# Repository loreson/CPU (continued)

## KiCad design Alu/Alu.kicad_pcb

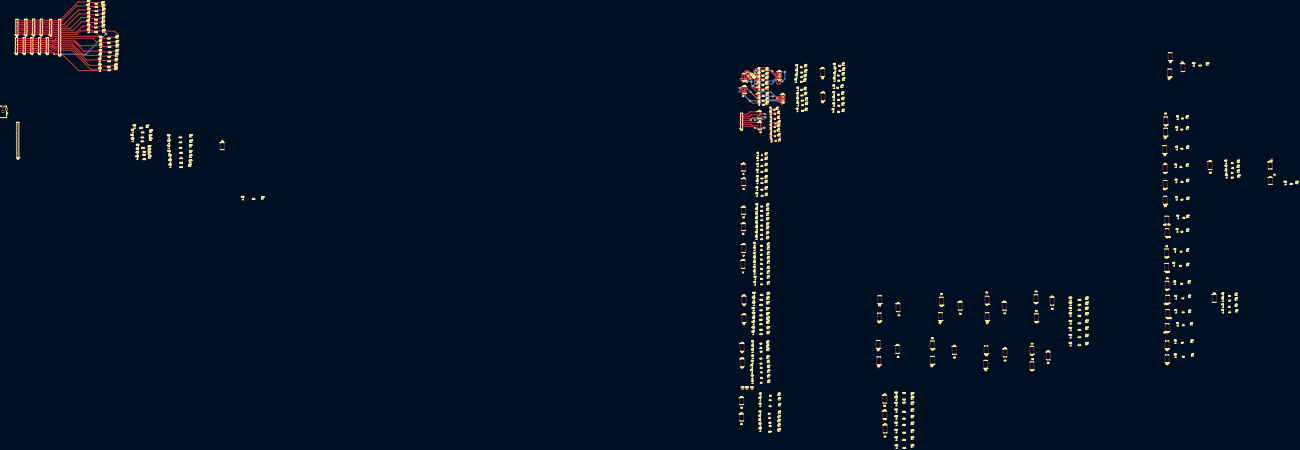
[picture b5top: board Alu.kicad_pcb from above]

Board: 4 copper layers, 642 parts (0 on the bottom side), 508 nets.

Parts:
C1, C2, C3, C4, C5, C8, C9, C10, C11, C12, C13, C14, C15, C16, C17, C18, C19, C20, C21, C22, C23, C24, C25, C26, C27, C28, C29, C30, C31, C32, C33, C34, C35, C36, C37, C38, C39, C40, C41, C42, C43, C44, C45, C46, C47, C48, C49, C50, C51, C52, C53, C54, C55, C56, C57, C58, C59, C60, C61, C62, C63, C64, C65, C66, C67, C68, C69, C70, C71: 100nF; C_0805_2012Metric
C6, C7: 100nF; C_0805_2012Metric_Pad1.29x1.40mm_HandSolder
D1, D2, D3, D4, D5, D6, D7, D8, D9, D10, D11, D12, D13, D14, D15, D16, D17, D18, D19, D20, D21, D22, D23, D24, D25, D26, D27, D28, D29, D30, D31, D32, D33, D34, D35, D36, D37, D38, D39, D40, D41, D42, D43, D44, D45, D46, D47, D48, D50, D51, D52, D53, D54, D55, D56, D58, D59, D60, D61, D62, D63, D64, D65, D66, D68, D69, D70, D71, D72, D73, D74, D75, D77, D78, D79, D80, D81, D82, D83, D84, D85, D86, D87, D88, D89, D90, D91, D92, D93, D94, D95, D96, D97, D98, D99, D100, D101, D102, D103, D104, D105, D106, D107, D108, D109, D110, D111, D112, D113, D114, D115, D116, D118, D119, D120, D121, D122, D123, D124, D125, D126, D127, D128, D129, D130, D131, D132, D133, D139, D140, D141, D142, D143, D144, D145, D146, D147, D148, D149, D150, D151, D152, D153, D154: RED; LED_0805_2012Metric_Pad1.12x1.40mm_HandSolder
D49, D57, D67, D76, D117, D134, D163, D164, D165, D167, D168: BLUE; LED_0805_2012Metric_Pad1.12x1.40mm_HandSolder
D135, D136, D137, D138, D166: GREEN; LED_0805_2012Metric_Pad1.12x1.40mm_HandSolder
J1, J3, J5, J6, J7, J9, J10, J11, J12, J13, J14: Conn_01x08; PinHeader_1x08_P2.54mm_Vertical_SMD_Pin1Right
J2: Barrel_Jack; BarrelJack_Horizontal
J4, J8: Conn_01x18; PinHeader_1x18_P2.54mm_Vertical_SMD_Pin1Left
Q1, Q2, Q3, Q4, Q5, Q6, Q7, Q8, Q9, Q10, Q11, Q12, Q13, Q14, Q15, Q16, Q17, Q18, Q19, Q20, Q21, Q22, Q23, Q24, Q25, Q26, Q27, Q28, Q29, Q30, Q31, Q32, Q33, Q34, Q35, Q36, Q37, Q38, Q39, Q40, Q41, Q42, Q43, Q44, Q45, Q46, Q47, Q48, Q49, Q50, Q51, Q52, Q53, Q54, Q55, Q56, Q57, Q58, Q59, Q60, Q61, Q62, Q63, Q64, Q65, Q66, Q67, Q68, Q69, Q70, Q71, Q72, Q73, Q74, Q75, Q76, Q77, Q78, Q79, Q80, Q81, Q82, Q83, Q84, Q85, Q86, Q87, Q88, Q89, Q90, Q91, Q92, Q93, Q94, Q95, Q96, Q97, Q98, Q99, Q100, Q101, Q102, Q103, Q104, Q105, Q106, Q107, Q108, Q109, Q110, Q111, Q112, Q113, Q114, Q115, Q116, Q117, Q118, Q119, Q120, Q121, Q122, Q123, Q124, Q125, Q126, Q127, Q128, Q129, Q130, Q131, Q132, Q133, Q134, Q135, Q136, Q137, Q138, Q139, Q140, Q141, Q142, Q143, Q144, Q145, Q146, Q147, Q148, Q149, Q150, Q151, Q152, Q153, Q154, Q163, Q164, Q165, Q166, Q167, Q168: 2N7002; SOT-23
R1, R2, R3, R4, R5, R6, R7, R8, R9, R10, R11, R12, R13, R14, R15, R16, R17, R18, R19, R20, R21, R22, R23, R24, R25, R26, R27, R28, R29, R30, R31, R32, R33, R34, R35, R36, R37, R38, R39, R40, R41, R42, R43, R44, R45, R46, R47, R48, R50, R51, R52, R53, R54, R55, R56, R58, R59, R60, R61, R62, R63, R64, R65, R66, R68, R69, R70, R71, R72, R73, R74, R75, R77, R78, R79, R80, R81, R82, R83, R84, R85, R86, R87, R88, R89, R90, R91, R92, R93, R94, R95, R96, R97, R98, R99, R100, R101, R102, R103, R104, R105, R106, R107, R108, R109, R110, R111, R112, R113, R114, R115, R116, R118, R119, R120, R121, R122, R123, R124, R125, R126, R127, R128, R129, R130, R131, R132, R133, R139, R140, R141, R142, R143, R144, R145, R146, R147, R148, R149, R150, R151, R152, R153, R154: 1k; R_0805_2012Metric
R49, R57, R67, R76, R117, R134, R163, R164, R165, R167, R168: 820R; R_0805_2012Metric_Pad1.29x1.40mm_HandSolder
R135, R136, R137, R138, R166: 1k; R_0805_2012Metric_Pad1.29x1.40mm_HandSolder
R155, R156: 0; R_1206_3216Metric_Pad1.39x1.80mm_HandSolder
R157, R158, R159, R160: 0; R_1806_4516Metric
U1, U5, U6: 74LS08; SOIC-14_3.9x8.7mm_P1.27mm
U2, U3: 74HC02; SOIC-14_3.9x8.7mm_P1.27mm
U4, U7: 74LS32; SOIC-14_3.9x8.7mm_P1.27mm
U8, U10, U11, U13, U14, U16, U17, U19, U20, U22, U23, U25, U26, U28, U29, U31, U32, U34: 74LS151; SOIC-16_3.9x9.9mm_P1.27mm
U9, U12, U15, U18, U21, U24, U27, U30, U33, U35, U36, U37, U53, U54: 74LS157; SOIC-16_3.9x9.9mm_P1.27mm
U41, U42, U71, U72: 74HC04; SOIC-14_3.9x8.7mm_P1.27mm
U43, U44: 74HC86; SOIC-14_3.9x8.7mm_P1.27mm
U45, U46, U47, U48, U49, U50, U51, U52, U73, U74: 74LS283; SOIC-16_3.9x9.9mm_P1.27mm
U55, U56, U57, U58, U59, U60, U61, U62, U63, U64, U65, U66, U67, U68, U69, U70: 74LS251; SOIC-16_3.9x9.9mm_P1.27mm

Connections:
/8-BIT_16-1MUX/16-2MUX0/Z0: Q68.1, U53.2, U55.5
/8-BIT_16-1MUX/16-2MUX0/Z1: Q69.1, U53.3, U56.5
/8-BIT_16-1MUX/16-2MUX1/Z0: Q70.1, U53.5, U57.5
/8-BIT_16-1MUX/16-2MUX1/Z1: Q71.1, U53.6, U58.5
/8-BIT_16-1MUX/16-2MUX2/Z0: Q72.1, U53.14, U59.5
/8-BIT_16-1MUX/16-2MUX2/Z1: Q73.1, U53.13, U60.5
/8-BIT_16-1MUX/16-2MUX3/Z0: Q74.1, U53.11, U61.5
/8-BIT_16-1MUX/16-2MUX3/Z1: Q75.1, U53.10, U62.5
/8-BIT_16-1MUX/16-2MUX4/Z0: Q77.1, U54.2, U63.5
/8-BIT_16-1MUX/16-2MUX4/Z1: Q78.1, U54.3, U64.5
/8-BIT_16-1MUX/16-2MUX5/Z0: Q79.1, U54.5, U65.5
/8-BIT_16-1MUX/16-2MUX5/Z1: Q80.1, U54.6, U66.5
/8-BIT_16-1MUX/16-2MUX6/Z0: Q81.1, U54.14, U67.5
/8-BIT_16-1MUX/16-2MUX6/Z1: Q82.1, U54.13, U68.5
/8-BIT_16-1MUX/16-2MUX7/Z0: Q83.1, U54.11, U69.5
/8-BIT_16-1MUX/16-2MUX7/Z1: Q84.1, U54.10, U70.5
/Bit0_X0: Q59.1, U51.4, U55.4
/Bit0_X1: Q8.1, U5.3, U55.3
/Bit0_X2: Q9.1, U4.3, U55.2
/Bit0_X3: Q25.1, U43.3, U55.1
/Bit0_X4: Q41.1, U47.4, U55.15
/Bit0_X5: Q101.1, U55.14, U73.4
/Bit0_X6: Q50.1, U49.4, U55.13
/Bit0_X7: Q93.1, R159.1, U55.12
/Bit0_X8: Q109.1, U12.4, U56.3, U56.4
/Bit0_X10: J1.8, J3.8, J5.8, J6.8, J7.8, J8.18, J14.8, Q147.1, U4.1, U5.1, U11.4, U13.4, U16.3, U19.2, U22.1, U25.15, U28.14, U31.13, U34.12, U35.2, U36.6, U43.1, U47.5, U49.5, U51.5, U56.2, U71.1, U73.5
/Bit0_X11: Q118.1, U36.4, U56.1, U56.15
/Bit1_X0: Q60.1, U51.1, U57.4
/Bit1_X1: Q1.1, U5.6, U57.3
/Bit1_X2: Q10.1, U4.6, U57.2
/Bit1_X3: Q26.1, U43.6, U57.1
/Bit1_X4: Q42.1, U47.1, U57.15
/Bit1_X5: Q102.1, U57.14, U73.1
/Bit1_X6: Q51.1, U49.1, U57.13
/Bit1_X7: Q94.1, R160.1, U57.12
/Bit1_X8: Q110.1, U15.4, U58.3, U58.4
/Bit1_X10: J1.7, J3.7, J5.7, J6.7, J7.7, J8.17, J14.7, Q148.1, U4.4, U5.4, U11.3, U14.4, U16.4, U19.3, U22.2, U25.1, U28.15, U31.14, U34.13, U36.2, U36.13, U43.4, U47.3, U49.3, U51.3, U58.2, U71.3, U73.3
/Bit1_X11: Q119.1, U36.7, U58.1, U58.15
/Bit2_X0: Q61.1, U51.13, U59.4
/Bit2_X1: Q2.1, U5.8, U59.3
/Bit2_X2: Q11.1, U4.8, U59.2
/Bit2_X3: Q27.1, U43.8, U59.1
/Bit2_X4: Q43.1, U47.13, U59.15
/Bit2_X5: Q103.1, U59.14, U73.13
/Bit2_X6: Q52.1, U49.13, U59.13
/Bit2_X7: Q95.1, R156.1, U59.12
/Bit2_X8: Q111.1, U18.4, U60.3, U60.4
/Bit2_X10: J1.6, J3.6, J5.6, J6.6, J7.6, J8.16, J14.6, Q149.1, U4.9, U5.9, U11.2, U14.3, U17.4, U19.4, U22.3, U25.2, U28.1, U31.15, U34.14, U36.5, U36.10, U43.9, U47.14, U49.14, U51.14, U60.2, U71.5, U73.14
/Bit2_X11: Q120.1, U36.12, U60.1, U60.15
/Bit3_X0: Q62.1, U51.10, U61.4
/Bit3_X1: Q3.1, U5.11, U61.3
/Bit3_X2: Q12.1, U4.11, U61.2
/Bit3_X3: Q28.1, U43.11, U61.1
/Bit3_X4: Q44.1, U47.10, U61.15
/Bit3_X5: Q104.1, U61.14, U73.10
/Bit3_X6: Q53.1, U49.10, U61.13
/Bit3_X7: Q96.1, U61.12, U71.8
/Bit3_X8: Q112.1, U21.4, U62.3, U62.4
/Bit3_X10: J1.5, J3.5, J5.5, J6.5, J7.5, J8.15, J14.5, Q150.1, U4.12, U5.12, U11.1, U14.2, U17.3, U20.4, U22.4, U25.3, U28.2, U31.1, U34.15, U36.14, U37.3, U43.12, U47.12, U49.12, U51.12, U62.2, U71.9, U73.12
/Bit3_X11: Q121.1, U36.9, U62.1, U62.15
/Bit4_X0: Q63.1, U52.4, U63.4
/Bit4_X1: Q4.1, U6.3, U63.3
/Bit4_X2: Q13.1, U7.3, U63.2
/Bit4_X3: Q29.1, U44.3, U63.1
/Bit4_X4: Q45.1, U48.4, U63.15
/Bit4_X5: Q105.1, U63.14, U74.4
/Bit4_X6: Q54.1, U50.4, U63.13
/Bit4_X7: Q97.1, U63.12, U71.10
/Bit4_X8: Q113.1, U24.4, U64.3, U64.4
/Bit4_X10: J1.4, J3.4, J5.4, J6.4, J7.4, J8.14, J14.4, Q151.1, U6.1, U7.1, U11.15, U14.1, U17.2, U20.3, U23.4, U25.4, U28.3, U31.2, U34.1, U36.11, U37.6, U44.1, U48.5, U50.5, U52.5, U64.2, U71.11, U74.5
/Bit4_X11: Q122.1, U37.4, U64.1, U64.15
/Bit5_X0: Q64.1, U52.1, U65.4
/Bit5_X1: Q5.1, U6.6, U65.3
/Bit5_X2: Q14.1, U7.6, U65.2
/Bit5_X3: Q30.1, U44.6, U65.1
/Bit5_X4: Q46.1, U48.1, U65.15
/Bit5_X5: Q106.1, U65.14, U74.1
/Bit5_X6: Q55.1, U50.1, U65.13
/Bit5_X7: Q98.1, U65.12, U71.12
/Bit5_X8: Q114.1, U27.4, U66.3, U66.4
/Bit5_X10: J1.3, J3.3, J5.3, J6.3, J7.3, J8.13, J14.3, Q152.1, U6.4, U7.4, U11.14, U14.15, U17.1, U20.2, U23.3, U26.4, U28.4, U31.3, U34.2, U37.2, U37.13, U44.4, U48.3, U50.3, U52.3, U66.2, U71.13, U74.3
/Bit5_X11: Q123.1, U37.7, U66.1, U66.15
/Bit6_X0: Q65.1, U52.13, U67.4
/Bit6_X1: Q6.1, U6.8, U67.3
/Bit6_X2: Q15.1, U7.8, U67.2
/Bit6_X3: Q31.1, U44.8, U67.1
/Bit6_X4: Q47.1, U48.13, U67.15
/Bit6_X5: Q107.1, U67.14, U74.13
/Bit6_X6: Q56.1, U50.13, U67.13
/Bit6_X7: Q99.1, U67.12, U72.2
/Bit6_X8: Q115.1, U30.4, U68.3, U68.4
/Bit6_X10: J1.2, J3.2, J5.2, J6.2, J7.2, J8.12, J14.2, Q153.1, U6.9, U7.9, U11.13, U14.14, U17.15, U20.1, U23.2, U26.3, U29.4, U31.4, U34.3, U37.5, U37.10, U44.9, U48.14, U50.14, U52.14, U68.2, U72.1, U74.14
/Bit6_X11: Q124.1, U37.12, U68.1, U68.15
/Bit7_X0: Q66.1, U52.10, U69.4
/Bit7_X1: Q7.1, U6.11, U69.3
/Bit7_X2: Q16.1, U7.11, U69.2
/Bit7_X3: Q32.1, U44.11, U69.1
/Bit7_X4: Q48.1, U48.10, U69.15
/Bit7_X5: Q108.1, U69.14, U74.10
/Bit7_X6: Q58.1, U50.10, U69.13
/Bit7_X7: Q100.1, U69.12, U72.4
/Bit7_X8: Q116.1, U33.4, U70.3, U70.4
/Bit7_X10: J1.1, J3.1, J5.1, J6.1, J7.1, J8.11, J14.1, Q154.1, U6.12, U7.12, U11.12, U14.13, U17.14, U20.15, U23.1, U26.2, U29.3, U32.4, U34.4, U35.3, U37.14, U44.12, U48.12, U50.12, U52.12, U70.2, U72.3, U74.12
/Bit7_X11: Q125.1, U37.9, U70.1, U70.15
/Cin: J4.18, Q165.1, U1.1
/CinE: J4.17, Q166.1, U1.2
/CinL: U1.3, U36.3, U37.11, U49.7, U51.7
/Cout: J4.16, Q163.1, Q168.1, U9.4
/Cout12-13: Q134.1, U10.14, U10.15, U35.4
/Cout_0: Q76.1, U8.4, U52.9
/Cout_4: Q57.1, U8.15, U48.9
/Cout_5: Q117.1, U8.14, U74.9
/Cout_6: Q67.1, U8.13, U50.9
/S0: J4.14, Q138.1, U9.1, U12.1, U15.1, U18.1, U21.1, U24.1, U27.1, U30.1, U33.1, U35.1, U36.1, U37.1, U53.1, U54.1
/S1: J4.13, Q137.1, U8.11, U10.11, U55.11, U56.11, U57.11, U58.11, U59.11, U60.11, U61.11, U62.11, U63.11, U64.11, U65.11, U66.11, U67.11, U68.11, U69.11, U70.11
/S2: J4.12, Q136.1, U8.10, U10.10, U55.10, U56.10, U57.10, U58.10, U59.10, U60.10, U61.10, U62.10, U63.10, U64.10, U65.10, U66.10, U67.10, U68.10, U69.10, U70.10
/S3: J4.11, Q135.1, U8.9, U10.9, U55.9, U56.9, U57.9, U58.9, U59.9, U60.9, U61.9, U62.9, U63.9, U64.9, U65.9, U66.9, U67.9, U68.9, U69.9, U70.9
/SUB_ADD/Y0: Q33.1, U45.4, U51.6
/SUB_ADD/Y1: Q34.1, U45.1, U51.2
/SUB_ADD/Y2: Q35.1, U45.13, U51.15
/SUB_ADD/Y3: Q36.1, U45.10, U51.11
/SUB_ADD/Y4: Q37.1, U46.4, U52.6
/SUB_ADD/Y5: Q38.1, U46.1, U52.2
/SUB_ADD/Y6: Q39.1, U46.13, U52.15
/SUB_ADD/Y7: Q40.1, U46.10, U52.11
/SUB_INC/C_OUT: Q49.1, U46.9
/SUB_INC/X0: Q17.1, R157.1, U45.5
/SUB_INC/X1: Q18.1, R158.1, U45.3
/SUB_INC/X2: Q19.1, R155.1, U45.14
/SUB_INC/X3: Q20.1, U41.8, U45.12
/SUB_INC/X4: Q21.1, U41.10, U46.5
/SUB_INC/X5: Q22.1, U41.12, U46.3
/SUB_INC/X6: Q23.1, U42.2, U46.14
/SUB_INC/X7: Q24.1, U42.4, U46.12
/Y0: J8.10, J9.8, J10.8, J11.8, J12.8, J13.8, Q126.1, U4.2, U5.2, U11.11, U13.11, U14.11, U16.11, U17.11, U19.11, U20.11, U22.11, U23.11, U25.11, U26.11, U28.11, U29.11, U31.11, U32.11, U34.11, U41.1, U43.2, U49.6
/Y1: J8.9, J9.7, J10.7, J11.7, J12.7, J13.7, Q127.1, U4.5, U5.5, U11.10, U13.10, U14.10, U16.10, U17.10, U19.10, U20.10, U22.10, U23.10, U25.10, U26.10, U28.10, U29.10, U31.10, U32.10, U34.10, U41.3, U43.5, U49.2
/Y2: J8.8, J9.6, J10.6, J11.6, J12.6, J13.6, Q128.1, U4.10, U5.10, U11.9, U13.9, U14.9, U16.9, U17.9, U19.9, U20.9, U22.9, U23.9, U25.9, U26.9, U28.9, U29.9, U31.9, U32.9, U34.9, U41.5, U43.10, U49.15
/Y3: J8.7, J9.5, J10.5, J11.5, J12.5, J13.5, Q129.1, U4.13, U5.13, U41.9, U43.13, U49.11
/Y4: J8.6, J9.4, J10.4, J11.4, J12.4, J13.4, Q130.1, U6.2, U7.2, U41.11, U44.2, U50.6
/Y5: J8.5, J9.3, J10.3, J11.3, J12.3, J13.3, Q131.1, U6.5, U7.5, U41.13, U44.5, U50.2
/Y6: J8.4, J9.2, J10.2, J11.2, J12.2, J13.2, Q132.1, U6.10, U7.10, U42.1, U44.10, U50.15
/Y7: J8.3, J9.1, J10.1, J11.1, J12.1, J13.1, Q133.1, U6.13, U7.13, U42.3, U44.13, U50.11
/Z0: J4.10, Q85.1, Q139.1, U2.2, U53.4
/Z1: J4.9, Q86.1, Q140.1, U2.3, U53.7
/Z2: J4.8, Q87.1, Q141.1, U2.5, U53.12
/Z3: J4.7, Q88.1, Q142.1, U2.6, U53.9
/Z4: J4.6, Q89.1, Q143.1, U2.8, U54.4
/Z5: J4.5, Q90.1, Q144.1, U2.9, U54.7
/Z6: J4.4, Q91.1, Q145.1, U2.11, U54.12
/Z7: J4.3, Q92.1, Q146.1, U2.12, U54.9
/ZFlag: J4.15, Q164.1, Q167.1, U3.10
GND: C1.2, C2.2, C3.2, C4.2, C5.2, C6.2, C7.2, C8.2, C9.2, C10.2, C11.2, C12.1, C13.1, C14.1, C15.1, C16.1, C17.1, C18.2, C19.2, C20.2, C21.2, C22.2, C23.2, C24.2, C25.2, C26.2, C27.2, C28.2, C29.2, C30.2, C31.2, C32.2, C33.2, C34.2, C35.2, C36.2, C37.2, C38.1, C39.1, C40.2, C41.2, C42.2, C43.2, C44.2, C45.2, C46.2, C47.2, C48.2, C49.2, C50.2, C51.2, C52.2, C53.2, C54.2, C55.2, C56.2, C57.2, C58.2, C59.2, C60.2, C61.2, C62.2, C63.2, C64.2, C65.2, C66.2, C67.2, C68.2, C69.2, C70.2, C71.2, J2.2, J2.3, J4.1, J8.1, Q1.2, Q2.2, Q3.2, Q4.2, Q5.2, Q6.2, Q7.2, Q8.2, Q9.2, Q10.2, Q11.2, Q12.2, Q13.2, Q14.2, Q15.2, Q16.2, Q17.2, Q18.2, Q19.2, Q20.2, Q21.2, Q22.2, Q23.2, Q24.2, Q25.2, Q26.2, Q27.2, Q28.2, Q29.2, Q30.2, Q31.2, Q32.2, Q33.2, Q34.2, Q35.2, Q36.2, Q37.2, Q38.2, Q39.2, Q40.2, Q41.2, Q42.2, Q43.2, Q44.2, Q45.2, Q46.2, Q47.2, Q48.2, Q49.2, Q50.2, Q51.2, Q52.2, Q53.2, Q54.2, Q55.2, Q56.2, Q57.2, Q58.2, Q59.2, Q60.2, Q61.2, Q62.2, Q63.2, Q64.2, Q65.2, Q66.2, Q67.2, Q68.2, Q69.2, Q70.2, Q71.2, Q72.2, Q73.2, Q74.2, Q75.2, Q76.2, Q77.2, Q78.2, Q79.2, Q80.2, Q81.2, Q82.2, Q83.2, Q84.2, Q85.2, Q86.2, Q87.2, Q88.2, Q89.2, Q90.2, Q91.2, Q92.2, Q93.2, Q94.2, Q95.2, Q96.2, Q97.2, Q98.2, Q99.2, Q100.2, Q101.2, Q102.2, Q103.2, Q104.2, Q105.2, Q106.2, Q107.2, Q108.2, Q109.2, Q110.2, Q111.2, Q112.2, Q113.2, Q114.2, Q115.2, Q116.2, Q117.2, Q118.2, Q119.2, Q120.2, Q121.2, Q122.2, Q123.2, Q124.2, Q125.2, Q126.2, Q127.2, Q128.2, Q129.2, Q130.2, Q131.2, Q132.2, Q133.2, Q134.2, Q135.2, Q136.2, Q137.2, Q138.2, Q139.2, Q140.2, Q141.2, Q142.2, Q143.2, Q144.2, Q145.2, Q146.2, Q147.2, Q148.2, Q149.2, Q150.2, Q151.2, Q152.2, Q153.2, Q154.2, Q163.2, Q164.2, Q165.2, Q166.2, Q167.2, Q168.2, U1.7, U2.7, U3.7, U3.11, U3.12, U4.7, U5.7, U6.7, U7.7, U8.1, U8.2, U8.3, U8.7, U8.8, U8.12, U9.5, U9.6, U9.8, U9.10, U9.11, U9.13, U9.14, U9.15, U10.1, U10.2, U10.3, U10.4, U10.7, U10.8, U10.12, U10.13, U11.7, U11.8, U12.5, U12.6, U12.8, U12.10, U12.11, U12.13, U12.14, U12.15, U13.1, U13.2, U13.3, U13.7, U13.8, U13.12, U13.13, U13.14, U13.15, U14.7, U14.8, U14.12, U15.5, U15.6, U15.8, U15.10, U15.11, U15.13, U15.14, U15.15, U16.1, U16.2, U16.7, U16.8, U16.12, U16.13, U16.14, U16.15, U17.7, U17.8, U17.12, U17.13, U18.5, U18.6, U18.8, U18.10, U18.11, U18.13, U18.14, U18.15, U19.1, U19.7, U19.8, U19.12, U19.13, U19.14, U19.15, U20.7, U20.8, U20.12, U20.13, U20.14, U21.5, U21.6, U21.8, U21.10, U21.11, U21.13, U21.14, U21.15, U22.7, U22.8, U22.12, U22.13, U22.14, U22.15, U23.7, U23.8, U23.12, U23.13, U23.14, U23.15, U24.5, U24.6, U24.8, U24.10, U24.11, U24.13, U24.14, U24.15, U25.7, U25.8, U25.12, U25.13, U25.14, U26.1, U26.7, U26.8, U26.12, U26.13, U26.14, U26.15, U27.5, U27.6, U27.8, U27.10, U27.11, U27.13, U27.14, U27.15, U28.7, U28.8, U28.12, U28.13, U29.1, U29.2, U29.7, U29.8, U29.12, U29.13, U29.14, U29.15, U30.5, U30.6, U30.8, U30.10, U30.11, U30.13, U30.14, U30.15, U31.7, U31.8, U31.12, U32.1, U32.2, U32.3, U32.7, U32.8, U32.12, U32.13, U32.14, U32.15, U33.5, U33.6, U33.8, U33.10, U33.11, U33.13, U33.14, U33.15, U34.7, U34.8, U35.5, U35.6, U35.8, U35.10, U35.11, U35.13, U35.14, U35.15, U36.8, U36.15, U37.8, U37.15, U41.7, U42.7, U43.7, U44.7, U45.2, U45.6, U45.8, U45.11, U45.15, U46.2, U46.6, U46.8, U46.11, U46.15, U47.7, U47.8, U48.8, U49.8, U50.8, U51.8, U52.8, U53.8, U53.15, U54.8, U54.15, U55.7, U55.8, U56.7, U56.8, U56.12, U56.13, U56.14, U57.7, U57.8, U58.7, U58.8, U58.12, U58.13, U58.14, U59.7, U59.8, U60.7, U60.8, U60.12, U60.13, U60.14, U61.7, U61.8, U62.7, U62.8, U62.12, U62.13, U62.14, U63.7, U63.8, U64.7, U64.8, U64.12, U64.13, U64.14, U65.7, U65.8, U66.7, U66.8, U66.12, U66.13, U66.14, U67.7, U67.8, U68.7, U68.8, U68.12, U68.13, U68.14, U69.7, U69.8, U70.7, U70.8, U70.12, U70.13, U70.14, U71.7, U72.7, U73.2, U73.6, U73.8, U73.11, U73.15, U74.2, U74.6, U74.8, U74.11, U74.15
unnamed: D1.1, R1.1
unnamed: D2.1, R2.1
unnamed: D3.1, R3.1
unnamed: D4.1, R4.1
unnamed: D5.1, R5.1
unnamed: D6.1, R6.1
unnamed: D7.1, R7.1
unnamed: D8.1, R8.1
unnamed: D9.1, R9.1
unnamed: D10.1, R10.1
unnamed: D11.1, R11.1
unnamed: D12.1, R12.1
unnamed: D13.1, R13.1
unnamed: D14.1, R14.1
unnamed: D15.1, R15.1
unnamed: D16.1, R16.1
unnamed: D17.1, R17.1
unnamed: D18.1, R18.1
unnamed: D19.1, R19.1
unnamed: D20.1, R20.1
unnamed: D21.1, R21.1
unnamed: D22.1, R22.1
unnamed: D23.1, R23.1
unnamed: D24.1, R24.1
unnamed: D25.1, R25.1
unnamed: D26.1, R26.1
unnamed: D27.1, R27.1
unnamed: D28.1, R28.1
unnamed: D29.1, R29.1
unnamed: D30.1, R30.1
unnamed: D31.1, R31.1
unnamed: D32.1, R32.1
unnamed: D33.1, R33.1
unnamed: D34.1, R34.1
unnamed: D35.1, R35.1
unnamed: D36.1, R36.1
unnamed: D37.1, R37.1
unnamed: D38.1, R38.1
unnamed: D39.1, R39.1
unnamed: D40.1, R40.1
unnamed: D41.1, R41.1
unnamed: D42.1, R42.1
unnamed: D43.1, R43.1
unnamed: D44.1, R44.1
unnamed: D45.1, R45.1
unnamed: D46.1, R46.1
unnamed: D47.1, R47.1
unnamed: D48.1, R48.1
unnamed: D49.1, R49.1
unnamed: D50.1, R50.1
unnamed: D51.1, R51.1
unnamed: D52.1, R52.1
unnamed: D53.1, R53.1
unnamed: D54.1, R54.1
unnamed: D55.1, R55.1
unnamed: D56.1, R56.1
unnamed: D57.1, R57.1
unnamed: D58.1, R58.1
unnamed: D59.1, R59.1
unnamed: D60.1, R60.1
unnamed: D61.1, R61.1
unnamed: D62.1, R62.1
unnamed: D63.1, R63.1
unnamed: D64.1, R64.1
unnamed: D65.1, R65.1
unnamed: D66.1, R66.1
unnamed: D67.1, R67.1
unnamed: D68.1, R68.1
unnamed: D69.1, R69.1
unnamed: D70.1, R70.1
unnamed: D71.1, R71.1
unnamed: D72.1, R72.1
unnamed: D73.1, R73.1
unnamed: D74.1, R74.1
unnamed: D75.1, R75.1
unnamed: D76.1, R76.1
unnamed: D77.1, R77.1
unnamed: D78.1, R78.1
unnamed: D79.1, R79.1
unnamed: D80.1, R80.1
unnamed: D81.1, R81.1
unnamed: D82.1, R82.1
unnamed: D83.1, R83.1
unnamed: D84.1, R84.1
unnamed: D85.1, R85.1
unnamed: D86.1, R86.1
unnamed: D87.1, R87.1
unnamed: D88.1, R88.1
unnamed: D89.1, R89.1
unnamed: D90.1, R90.1
unnamed: D91.1, R91.1
unnamed: D92.1, R92.1
unnamed: D93.1, R93.1
unnamed: D94.1, R94.1
unnamed: D95.1, R95.1
unnamed: D96.1, R96.1
unnamed: D97.1, R97.1
unnamed: D98.1, R98.1
unnamed: D99.1, R99.1
unnamed: D100.1, R100.1
unnamed: D101.1, R101.1
unnamed: D102.1, R102.1
unnamed: D103.1, R103.1
unnamed: D104.1, R104.1
unnamed: D105.1, R105.1
unnamed: D106.1, R106.1
unnamed: D107.1, R107.1
unnamed: D108.1, R108.1
unnamed: D109.1, R109.1
unnamed: D110.1, R110.1
unnamed: D111.1, R111.1
unnamed: D112.1, R112.1
unnamed: D113.1, R113.1
unnamed: D114.1, R114.1
unnamed: D115.1, R115.1
unnamed: D116.1, R116.1
unnamed: D117.1, R117.1
unnamed: D118.1, R118.1
unnamed: D119.1, R119.1
unnamed: D120.1, R120.1
unnamed: D121.1, R121.1
unnamed: D122.1, R122.1
unnamed: D123.1, R123.1
unnamed: D124.1, R124.1
unnamed: D125.1, R125.1
unnamed: D126.1, R126.1
unnamed: D127.1, R127.1
unnamed: D128.1, R128.1
unnamed: D129.1, R129.1
unnamed: D130.1, R130.1
unnamed: D131.1, R131.1
unnamed: D132.1, R132.1
unnamed: D133.1, R133.1
unnamed: D134.1, R134.1
unnamed: D135.1, R135.1
unnamed: D136.1, R136.1
unnamed: D137.1, R137.1
unnamed: D138.1, R138.1
unnamed: D139.1, R139.1
unnamed: D140.1, R140.1
unnamed: D141.1, R141.1
unnamed: D142.1, R142.1
unnamed: D143.1, R143.1
unnamed: D144.1, R144.1
unnamed: D145.1, R145.1
unnamed: D146.1, R146.1
unnamed: D147.1, R147.1
unnamed: D148.1, R148.1
unnamed: D149.1, R149.1
unnamed: D150.1, R150.1
unnamed: D151.1, R151.1
unnamed: D152.1, R152.1
unnamed: D153.1, R153.1
unnamed: D154.1, R154.1
unnamed: D163.1, R163.1
unnamed: D164.1, R164.1
unnamed: D165.1, R165.1
unnamed: D166.1, R166.1
unnamed: D167.1, R167.1
unnamed: D168.1, R168.1
unnamed: Q1.3, R1.2
unnamed: Q2.3, R2.2
unnamed: Q3.3, R3.2
unnamed: Q4.3, R4.2
unnamed: Q5.3, R5.2
unnamed: Q6.3, R6.2
unnamed: Q7.3, R7.2
unnamed: Q8.3, R8.2
unnamed: Q9.3, R9.2
unnamed: Q10.3, R10.2
unnamed: Q11.3, R11.2
unnamed: Q12.3, R12.2
unnamed: Q13.3, R13.2
unnamed: Q14.3, R14.2
unnamed: Q15.3, R15.2
unnamed: Q16.3, R16.2
unnamed: Q17.3, R17.2
unnamed: Q18.3, R18.2
unnamed: Q19.3, R19.2
unnamed: Q20.3, R20.2
unnamed: Q21.3, R21.2
unnamed: Q22.3, R22.2
unnamed: Q23.3, R23.2
unnamed: Q24.3, R24.2
unnamed: Q25.3, R25.2
unnamed: Q26.3, R26.2
unnamed: Q27.3, R27.2
unnamed: Q28.3, R28.2
unnamed: Q29.3, R29.2
unnamed: Q30.3, R30.2
unnamed: Q31.3, R31.2
unnamed: Q32.3, R32.2
unnamed: Q33.3, R33.2
unnamed: Q34.3, R34.2
unnamed: Q35.3, R35.2
unnamed: Q36.3, R36.2
unnamed: Q37.3, R37.2
unnamed: Q38.3, R38.2
unnamed: Q39.3, R39.2
unnamed: Q40.3, R40.2
unnamed: Q41.3, R41.2
unnamed: Q42.3, R42.2
unnamed: Q43.3, R43.2
unnamed: Q44.3, R44.2
unnamed: Q45.3, R45.2
unnamed: Q46.3, R46.2
unnamed: Q47.3, R47.2
unnamed: Q48.3, R48.2
unnamed: Q49.3, R49.2
unnamed: Q50.3, R50.2
unnamed: Q51.3, R51.2
unnamed: Q52.3, R52.2
unnamed: Q53.3, R53.2
unnamed: Q54.3, R54.2
unnamed: Q55.3, R55.2
unnamed: Q56.3, R56.2
unnamed: Q57.3, R57.2
unnamed: Q58.3, R58.2
unnamed: Q59.3, R59.2
unnamed: Q60.3, R60.2
unnamed: Q61.3, R61.2
unnamed: Q62.3, R62.2
unnamed: Q63.3, R63.2
unnamed: Q64.3, R64.2
unnamed: Q65.3, R65.2
unnamed: Q66.3, R66.2
unnamed: Q67.3, R67.2
unnamed: Q68.3, R68.2
unnamed: Q69.3, R69.2
unnamed: Q70.3, R70.2
unnamed: Q71.3, R71.2
unnamed: Q72.3, R72.2
unnamed: Q73.3, R73.2
unnamed: Q74.3, R74.2
unnamed: Q75.3, R75.2
unnamed: Q76.3, R76.2
unnamed: Q77.3, R77.2
unnamed: Q78.3, R78.2
unnamed: Q79.3, R79.2
unnamed: Q80.3, R80.2
unnamed: Q81.3, R81.2
unnamed: Q82.3, R82.2
unnamed: Q83.3, R83.2
unnamed: Q84.3, R84.2
unnamed: Q85.3, R85.2
unnamed: Q86.3, R86.2
unnamed: Q87.3, R87.2
unnamed: Q88.3, R88.2
unnamed: Q89.3, R89.2
unnamed: Q90.3, R90.2
unnamed: Q91.3, R91.2
unnamed: Q92.3, R92.2
unnamed: Q93.3, R93.2
unnamed: Q94.3, R94.2
unnamed: Q95.3, R95.2
unnamed: Q96.3, R96.2
unnamed: Q97.3, R97.2
unnamed: Q98.3, R98.2
unnamed: Q99.3, R99.2
unnamed: Q100.3, R100.2
unnamed: Q101.3, R101.2
unnamed: Q102.3, R102.2
unnamed: Q103.3, R103.2
unnamed: Q104.3, R104.2
unnamed: Q105.3, R105.2
unnamed: Q106.3, R106.2
unnamed: Q107.3, R107.2
unnamed: Q108.3, R108.2
unnamed: Q109.3, R109.2
unnamed: Q110.3, R110.2
unnamed: Q111.3, R111.2
unnamed: Q112.3, R112.2
unnamed: Q113.3, R113.2
unnamed: Q114.3, R114.2
unnamed: Q115.3, R115.2
unnamed: Q116.3, R116.2
unnamed: Q117.3, R117.2
unnamed: Q118.3, R118.2
unnamed: Q119.3, R119.2
unnamed: Q120.3, R120.2
unnamed: Q121.3, R121.2
unnamed: Q122.3, R122.2
unnamed: Q123.3, R123.2
unnamed: Q124.3, R124.2
unnamed: Q125.3, R125.2
unnamed: Q126.3, R126.2
unnamed: Q127.3, R127.2
unnamed: Q128.3, R128.2
unnamed: Q129.3, R129.2
unnamed: Q130.3, R130.2
unnamed: Q131.3, R131.2
unnamed: Q132.3, R132.2
unnamed: Q133.3, R133.2
unnamed: Q134.3, R134.2
unnamed: Q135.3, R135.2
unnamed: Q136.3, R136.2
unnamed: Q137.3, R137.2
unnamed: Q138.3, R138.2
unnamed: Q139.3, R139.2
unnamed: Q140.3, R140.2
unnamed: Q141.3, R141.2
unnamed: Q142.3, R142.2
unnamed: Q143.3, R143.2
unnamed: Q144.3, R144.2
unnamed: Q145.3, R145.2
unnamed: Q146.3, R146.2
unnamed: Q147.3, R147.2
unnamed: Q148.3, R148.2
unnamed: Q149.3, R149.2
unnamed: Q150.3, R150.2
unnamed: Q151.3, R151.2
unnamed: Q152.3, R152.2
unnamed: Q153.3, R153.2
unnamed: Q154.3, R154.2
unnamed: Q163.3, R163.2
unnamed: Q164.3, R164.2
unnamed: Q165.3, R165.2
unnamed: Q166.3, R166.2
unnamed: Q167.3, R167.2
unnamed: Q168.3, R168.2
unnamed: R155.2, U41.6
unnamed: R156.2, U71.6
unnamed: R157.2, U41.2
unnamed: R158.2, U41.4
unnamed: R159.2, U71.2
unnamed: R160.2, U71.4
unnamed: U2.1, U3.2
unnamed: U2.4, U3.3
unnamed: U2.10, U3.5
unnamed: U2.13, U3.6
unnamed: U3.1, U3.8
unnamed: U3.4, U3.9
unnamed: U8.5, U9.2
unnamed: U9.3, U10.5
unnamed: U11.5, U12.2
unnamed: U12.3, U13.5
unnamed: U14.5, U15.2
unnamed: U15.3, U16.5
unnamed: U17.5, U18.2
unnamed: U18.3, U19.5
unnamed: U20.5, U21.2
unnamed: U21.3, U22.5
unnamed: U23.5, U24.2
unnamed: U24.3, U25.5
unnamed: U26.5, U27.2
unnamed: U27.3, U28.5
unnamed: U29.5, U30.2
unnamed: U30.3, U31.5
unnamed: U32.5, U33.2
unnamed: U33.3, U34.5
unnamed: U45.9, U46.7
unnamed: U47.9, U48.7
unnamed: U49.9, U50.7
unnamed: U51.9, U52.7
unnamed: U73.9, U74.7
VCC: C1.1, C2.1, C3.1, C4.1, C5.1, C6.1, C7.1, C8.1, C9.1, C10.1, C11.1, C12.2, C13.2, C14.2, C15.2, C16.2, C17.2, C18.1, C19.1, C20.1, C21.1, C22.1, C23.1, C24.1, C25.1, C26.1, C27.1, C28.1, C29.1, C30.1, C31.1, C32.1, C33.1, C34.1, C35.1, C36.1, C37.1, C38.2, C39.2, C40.1, C41.1, C42.1, C43.1, C44.1, C45.1, C46.1, C47.1, C48.1, C49.1, C50.1, C51.1, C52.1, C53.1, C54.1, C55.1, C56.1, C57.1, C58.1, C59.1, C60.1, C61.1, C62.1, C63.1, C64.1, C65.1, C66.1, C67.1, C68.1, C69.1, C70.1, C71.1, D1.2, D2.2, D3.2, D4.2, D5.2, D6.2, D7.2, D8.2, D9.2, D10.2, D11.2, D12.2, D13.2, D14.2, D15.2, D16.2, D17.2, D18.2, D19.2, D20.2, D21.2, D22.2, D23.2, D24.2, D25.2, D26.2, D27.2, D28.2, D29.2, D30.2, D31.2, D32.2, D33.2, D34.2, D35.2, D36.2, D37.2, D38.2, D39.2, D40.2, D41.2, D42.2, D43.2, D44.2, D45.2, D46.2, D47.2, D48.2, D49.2, D50.2, D51.2, D52.2, D53.2, D54.2, D55.2, D56.2, D57.2, D58.2, D59.2, D60.2, D61.2, D62.2, D63.2, D64.2, D65.2, D66.2, D67.2, D68.2, D69.2, D70.2, D71.2, D72.2, D73.2, D74.2, D75.2, D76.2, D77.2, D78.2, D79.2, D80.2, D81.2, D82.2, D83.2, D84.2, D85.2, D86.2, D87.2, D88.2, D89.2, D90.2, D91.2, D92.2, D93.2, D94.2, D95.2, D96.2, D97.2, D98.2, D99.2, D100.2, D101.2, D102.2, D103.2, D104.2, D105.2, D106.2, D107.2, D108.2, D109.2, D110.2, D111.2, D112.2, D113.2, D114.2, D115.2, D116.2, D117.2, D118.2, D119.2, D120.2, D121.2, D122.2, D123.2, D124.2, D125.2, D126.2, D127.2, D128.2, D129.2, D130.2, D131.2, D132.2, D133.2, D134.2, D135.2, D136.2, D137.2, D138.2, D139.2, D140.2, D141.2, D142.2, D143.2, D144.2, D145.2, D146.2, D147.2, D148.2, D149.2, D150.2, D151.2, D152.2, D153.2, D154.2, D163.2, D164.2, D165.2, D166.2, D167.2, D168.2, J2.1, J4.2, J8.2, U1.4, U1.5, U1.9, U1.10, U1.12, U1.13, U1.14, U2.14, U3.14, U4.14, U5.14, U6.14, U7.14, U8.16, U9.16, U10.16, U11.16, U12.16, U13.16, U14.16, U15.16, U16.16, U17.16, U18.16, U19.16, U20.16, U21.16, U22.16, U23.16, U24.16, U25.16, U26.16, U27.16, U28.16, U29.16, U30.16, U31.16, U32.16, U33.16, U34.16, U35.16, U36.16, U37.16, U41.14, U42.5, U42.9, U42.11, U42.13, U42.14, U43.14, U44.14, U45.7, U45.16, U46.16, U47.2, U47.6, U47.11, U47.15, U47.16, U48.2, U48.6, U48.11, U48.15, U48.16, U49.16, U50.16, U51.16, U52.16, U53.16, U54.16, U55.16, U56.16, U57.16, U58.16, U59.16, U60.16, U61.16, U62.16, U63.16, U64.16, U65.16, U66.16, U67.16, U68.16, U69.16, U70.16, U71.14, U72.5, U72.9, U72.11, U72.13, U72.14, U73.7, U73.16, U74.16

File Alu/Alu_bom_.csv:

Component,Description,Part,References,Value,Footprint,Quantity Per PCB,Datasheet,Spice_Netlist_Enabled,Spice_Lib_File,Spice_Model,Spice_Primitive
1,Unpolarized capacitor,C_Small,C1 C2 C3 C4 C5 C8 C9 C10 C11 C12 C13 C14 C15 C16 C17 C18 C19 C20 C21 C22 C23 C24 C25 C26 C27 C28 C29 C30 C31 C32 C33 C34 C35 C36 C37 C38 C39 C40 C41 C42 C43 C44 C45 C46 C47 C48 C49 C50 C51 C52 C53 C54 C55 C56 C57 C58 C59 C60 C61 C62 C63 C64 C65 C66 C67 C68 C69 C70 C71,100nF,C_0805_2012Metric,69,,,,,
2,LED generic,LED,D49 D57 D67 D76 D117 D134 D163 D164 D165 D167 D168,BLUE,LED_0805_2012Metric_Pad1.12x1.40mm_HandSolder,11,,,,,
3,LED generic,LED,D135 D136 D137 D138 D166,GREEN,LED_0805_2012Metric_Pad1.12x1.40mm_HandSolder,5,,,,,
4,LED generic,LED,D1 D2 D3 D4 D5 D6 D7 D8 D17 D18 D19 D20 D21 D22 D23 D24 D25 D26 D27 D28 D29 D30 D31 D32 D33 D34 D35 D36 D37 D38 D39 D40 D41 D42 D43 D44 D45 D46 D47 D48 D50 D51 D52 D53 D54 D55 D56 D58 D59 D60 D61 D62 D63 D64 D65 D66 D68 D69 D70 D71 D72 D73 D74 D75 D77 D78 D79 D80 D81 D82 D83 D84 D85 D86 D87 D88 D89 D90 D91 D92 D93 D94 D95 D96 D97 D98 D99 D100 D101 D102 D103 D104 D105 D106 D107 D108 D109 D110 D111 D112 D113 D114 D115 D116 D118 D119 D120 D121 D122 D123 D124 D125 D126 D127 D128 D129 D130 D131 D132 D133 D139 D140 D141 D142 D143 D144 D145 D146 D147 D148 D149 D150 D151 D152 D153 D154 D155 D156 D157 D158 D159 D160 D161 D162,RED,LED_0805_2012Metric_Pad1.12x1.40mm_HandSolder,144,,,,,
5,DC Barrel Jack,Barrel_Jack,J2,Barrel_Jack,BarrelJack_Horizontal,1,,,,,
6,"Generic connector, single row, 01x34, script generated (kicad-library-utils/schlib/autogen/connector/)",Conn_01x34,J1,Conn_01x34,PinHeader_1x34_P2.54mm_Vertical_SMD_Pin1Right,1,,,,,
7,"50V Vds, 0.22A Id, N-channel MOSFET, SOT-23",2N7002,Q1 Q2 Q3 Q4 Q5 Q6 Q7 Q8 Q17 Q18 Q19 Q20 Q21 Q22 Q23 Q24 Q25 Q26 Q27 Q28 Q29 Q30 Q31 Q32 Q33 Q34 Q35 Q36 Q37 Q38 Q39 Q40 Q41 Q42 Q43 Q44 Q45 Q46 Q47 Q48 Q49 Q50 Q51 Q52 Q53 Q54 Q55 Q56 Q57 Q58 Q59 Q60 Q61 Q62 Q63 Q64 Q65 Q66 Q67 Q68 Q69 Q70 Q71 Q72 Q73 Q74 Q75 Q76 Q77 Q78 Q79 Q80 Q81 Q82 Q83 Q84 Q85 Q86 Q87 Q88 Q89 Q90 Q91 Q92 Q93 Q94 Q95 Q96 Q97 Q98 Q99 Q100 Q101 Q102 Q103 Q104 Q105 Q106 Q107 Q108 Q109 Q110 Q111 Q112 Q113 Q114 Q115 Q116 Q117 Q118 Q119 Q120 Q121 Q122 Q123 Q124 Q125 Q126 Q127 Q128 Q129 Q130 Q131 Q132 Q133 Q134 Q135 Q136 Q137 Q138 Q139 Q140 Q141 Q142 Q143 Q144 Q145 Q146 Q147 Q148 Q149 Q150 Q151 Q152 Q153 Q154 Q155 Q156 Q157 Q158 Q159 Q160 Q161 Q162 Q163 Q164 Q165 Q166 Q167 Q168,2N7002,SOT-23,160,https://www.fairchildsemi.com/datasheets/2N/2N7002.pdf,,,,
8,Resistor,R,R1 R2 R3 R4 R5 R6 R7 R8 R17 R18 R19 R20 R21 R22 R23 R24 R25 R26 R27 R28 R29 R30 R31 R32 R33 R34 R35 R36 R37 R38 R39 R40 R41 R42 R43 R44 R45 R46 R47 R48 R50 R51 R52 R53 R54 R55 R56 R58 R59 R60 R61 R62 R63 R64 R65 R66 R68 R69 R70 R71 R72 R73 R74 R75 R77 R78 R79 R80 R81 R82 R83 R84 R85 R86 R87 R88 R89 R90 R91 R92 R93 R94 R95 R96 R97 R98 R99 R100 R101 R102 R103 R104 R105 R106 R107 R108 R109 R110 R111 R112 R113 R114 R115 R116 R118 R119 R120 R121 R122 R123 R124 R125 R126 R127 R128 R129 R130 R131 R132 R133 R139 R140 R141 R142 R143 R144 R145 R146 R147 R148 R149 R150 R151 R152 R153 R154 R155 R156 R157 R158 R159 R160 R161 R162,1k,R_0805_2012Metric,144,,,,,
9,Resistor,R,R135 R136 R137 R138 R166,1k,R_0815_2038Metric_Pad1.64x4.00mm_HandSolder,5,,,,,
10,Resistor,R,R49 R57 R67 R76 R117 R134 R163 R164 R165 R167 R168,820R,R_0805_2012Metric_Pad1.29x1.40mm_HandSolder,11,,,,,
11,quad 2-input NOR gate,74HC02,U2 U3,74HC02,SOIC-14_3.9x8.7mm_P1.27mm,2,http://www.ti.com/lit/gpn/sn74hc02,,,,
12,hex inverter,74HC04,U41 U42 U71 U72,74HC04,SOIC-14_3.9x8.7mm_P1.27mm,4,http://www.nxp.com/documents/data_sheet/74HC_HCT04.pdf,,,,
13,Quad 2-input XOR,74HC86,U43 U44,74HC86,SOIC-14_3.9x8.7mm_P1.27mm,2,http://www.ti.com/lit/gpn/sn74HC86,,,,
14,Quad And2,74LS08,U1,74LS08,,1,http://www.ti.com/lit/gpn/sn74LS08,,,,
15,Quad And2,74LS08,U5 U6,74LS08,SOIC-14_3.9x8.7mm_P1.27mm,2,http://www.ti.com/lit/gpn/sn74LS08,,,,
16,Multiplexer 8 to 1,74LS151,U8 U10 U11 U13 U14 U16 U17 U19 U20 U22 U23 U25 U26 U28 U29 U31 U32 U34,74LS151,SOIC-16_3.9x9.9mm_P1.27mm,18,http://www.ti.com/lit/gpn/sn74LS151,Y,74hc.lib,74HC151,X
17,Quad 2 to 1 line Multiplexer,74LS157,U9 U12 U15 U18 U21 U24 U27 U30 U33,74LS157,SOIC-16_3.9x9.9mm_P1.27mm,9,http://www.ti.com/lit/gpn/sn74LS157,,,,
18,Quad 2 to 1 line Multiplexer,74LS157,U35 U36 U37 U53 U54,74LS157,,5,http://www.ti.com/lit/gpn/sn74LS157,,,,
19,"Multiplexer 8 to 1, 3-state Outputs",74LS251,U55 U56 U57 U58 U59 U60 U61 U62 U63 U64 U65 U66 U67 U68 U69 U70,74LS251,,16,http://www.ti.com/lit/gpn/sn74LS251,,,,
20,4-bit full Adder,74LS283,U45 U46 U47 U48 U49 U50 U51 U52 U73 U74,74LS283,,10,http://www.ti.com/lit/gpn/sn74LS283,,,,
21,Quad 2-input OR,74LS32,U4 U7,74LS32,SOIC-14_3.9x8.7mm_P1.27mm,2,http://www.ti.com/lit/gpn/sn74LS32,,,,





Component Groups:,21
Component Count:,622
Fitted Components:,622
Number of PCBs:,1
Total components:,622
Schematic Version:,
Schematic Date:,
BoM Date:,Do 14 Jun 2018 00:03:24 CEST
Schematic Source:,/home/christian/CPU/Alu/Alu.sch
KiCad Version:,Eeschema 5.0.0-rc2-be01b52~65~ubuntu18.04.1

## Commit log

2017-11-21 Wiring of Registers to MUX
2017-11-22 register verkabelung
2018-05-01 A new beginning
2018-05-01 pins
2018-05-01 adder
2018-05-01 multiplexer for instruction selection
2018-05-01 wiring
2018-05-01 more wiring and correction of swapped pins
2018-05-02 SPICE capacitance and ground symbols
2018-05-02 fixed duplicate names
2018-05-02 NC-symbols
2018-05-02 spice libs from the internet, opened with new kicad 5.0.0, added spice models to components
2018-05-02 now the libs are realy there
2018-05-12 lots of work done
2018-05-12 forgotten files
2018-05-20 fixed errors
2018-05-21 message
2018-06-11 seperated alu
2018-06-11 footprints
2018-06-14 started routing
2018-06-14 coniued layouting
2018-06-15 started routing :)
2018-06-19 split pcbs
